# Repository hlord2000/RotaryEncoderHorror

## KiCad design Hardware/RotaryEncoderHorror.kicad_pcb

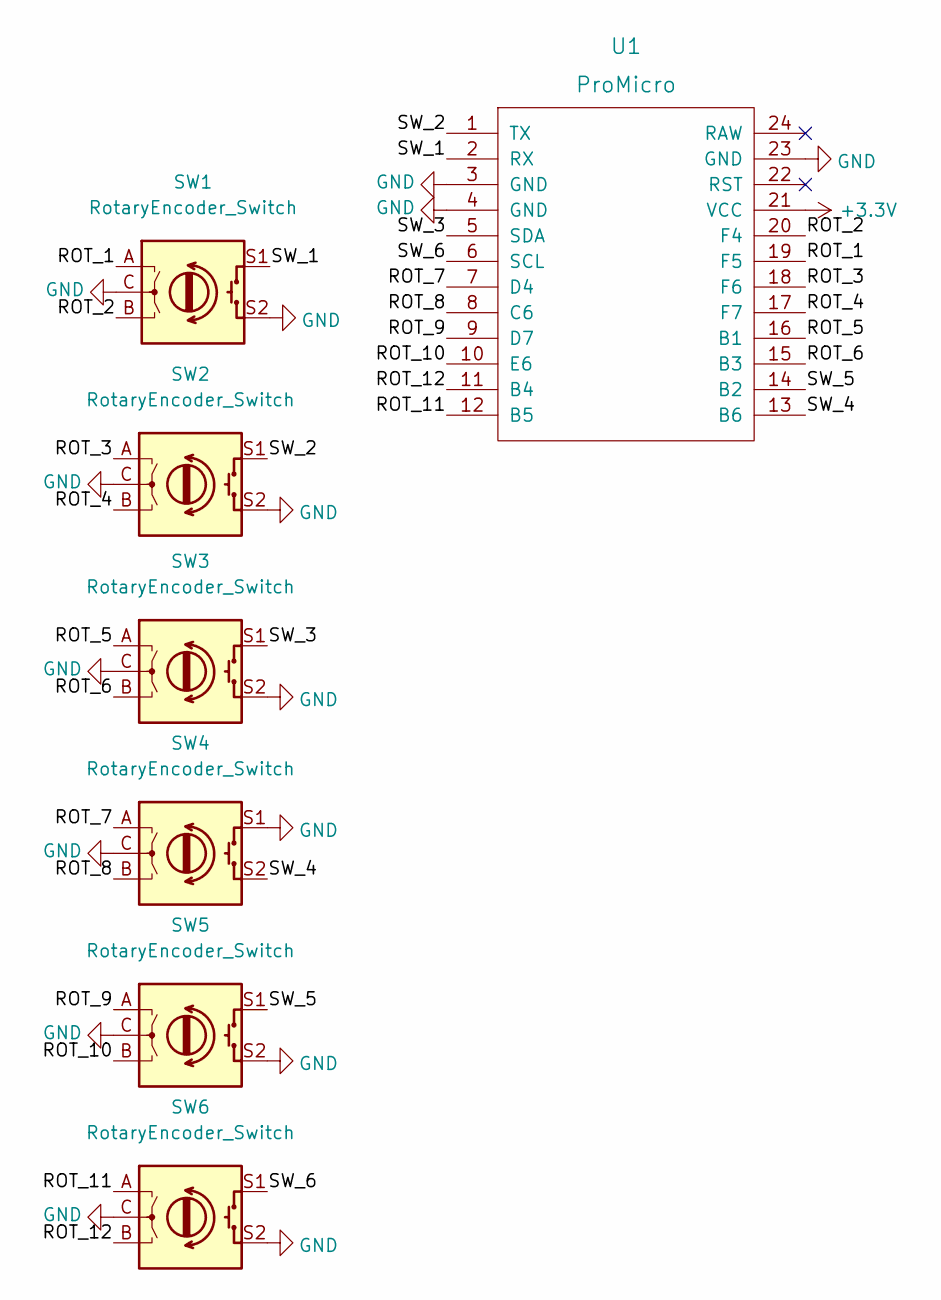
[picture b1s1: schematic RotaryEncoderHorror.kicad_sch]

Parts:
SW1, SW2, SW3, SW4, SW5, SW6: RotaryEncoder_Switch; RotaryEncoder_Alps_EC11E-Switch_Vertical_H20mm
U1: ProMicro

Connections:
+3V3: U1.21 (VCC)
/ROT_1: SW1.A, U1.19 (F5)
/ROT_2: SW1.B, U1.20 (F4)
/ROT_3: SW2.A, U1.18 (F6)
/ROT_4: SW2.B, U1.17 (F7)
/ROT_5: SW3.A, U1.16 (B1)
/ROT_6: SW3.B, U1.15 (B3)
/ROT_7: SW4.A, U1.7 (D4)
/ROT_8: SW4.B, U1.8 (C6)
/ROT_9: SW5.A, U1.9 (D7)
/ROT_10: SW5.B, U1.10 (E6)
/ROT_11: SW6.A, U1.12 (B5)
/ROT_12: SW6.B, U1.11 (B4)
/SW_1: SW1.S1, U1.2 (RX)
/SW_2: SW2.S1, U1.1 (TX)
/SW_3: SW3.S1, U1.5 (SDA)
/SW_4: SW4.S2, U1.13 (B6)
/SW_5: SW5.S1, U1.14 (B2)
/SW_6: SW6.S1, U1.6 (SCL)
GND: SW1.C, SW1.S2, SW2.C, SW2.S2, SW3.C, SW3.S2, SW4.C, SW4.S1, SW5.C, SW5.S2, SW6.C, SW6.S2, U1.3 (GND), U1.4 (GND), U1.23 (GND)

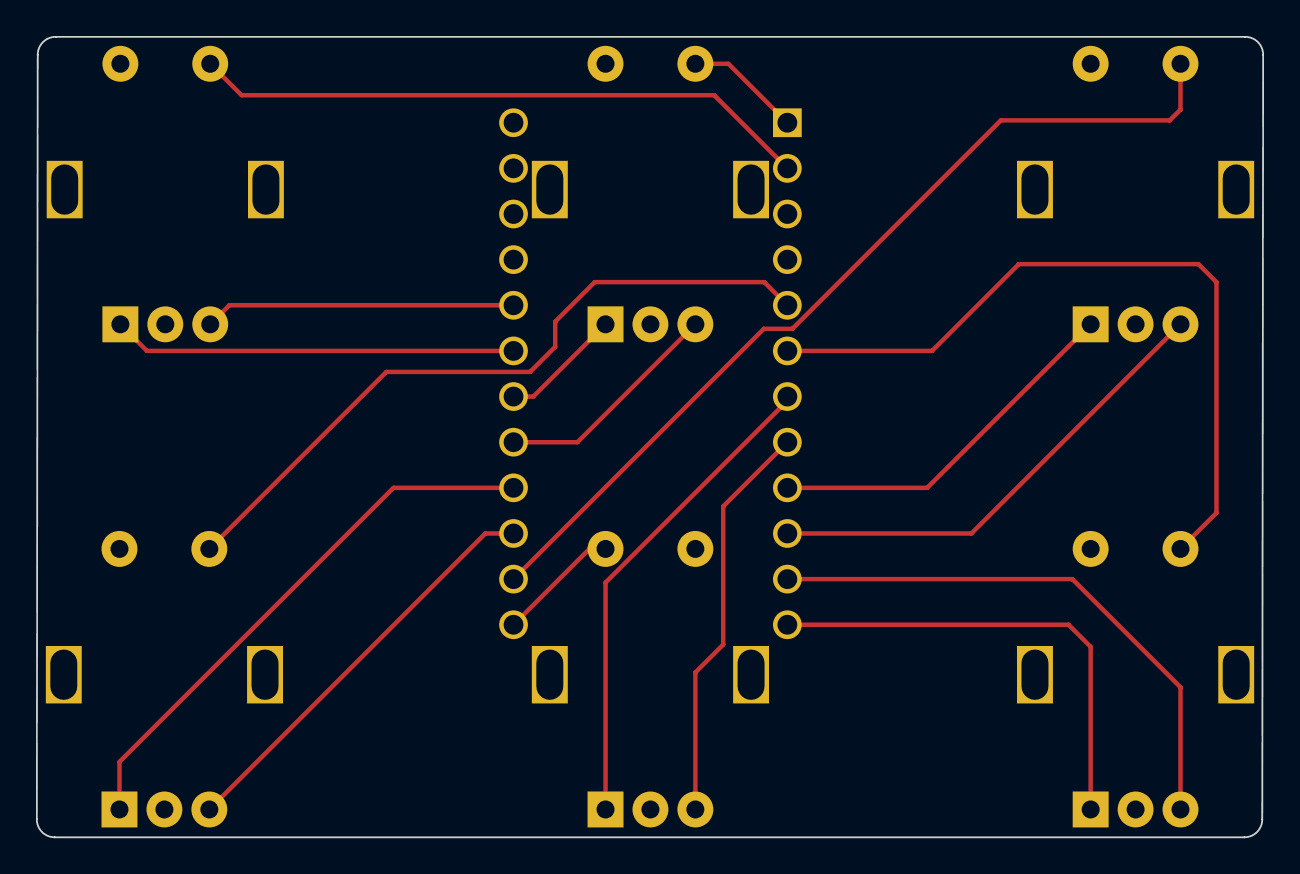
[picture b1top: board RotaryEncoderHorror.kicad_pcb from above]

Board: 2 copper layers, 68.2 x 44.5 mm, 7 parts (1 on the bottom side), 19 nets.

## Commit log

2022-06-12 Initial commit.
